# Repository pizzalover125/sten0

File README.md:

# sten0

sten0 is a minimalist stenography keyboard. it was meant to defeat the industry standard Uni v4 which is overpriced and unsymmetrical. it uses a 2-layer PCB and KMK firmware that converts to stenography with the industry-standard Plover firmware. 

### what is steno?
traditional stenography keyboards are keyboards used by transcribers in a courtroom to type extremely fast. hobbyists and now companies have created their own versions of steno keyboards. one can easily get 200 wpm using steno, demonstrated in the video here: https://www.youtube.com/watch?v=l8SWkR5y774. 

steno works by pressing multiple keys at once to create "chords" which create words. each key is associated with a specific sound. for example, to write "cat" press "K A T" all at once.

the company, stenokeyboards.com, is the leader of the steno industry with products that are pretty cool, but extremely expensive. worst of all, they are closed source. i wanted to make something better for cheaper.

### PCB + Schematic
I used KiCad 10.0 for the PCB design. The silkscreen art was created using https://www.fontspace.com/ and inputted to KiCad using the built-in Image Convertor tool.

### CAD
I used Onshape for the entire CAD. It features a front plate and a back plate. It is only 255.4 mm wide at its widest point, making it printable on a standard Bambu Lab A1 or any Bambu Lab 3d printer. Can be viewed here! https://cad.onshape.com/documents/f60da929d98268854f5791b9/w/b980d7f138533dbdb870e5ad/e/3b5277e683bbd7090a7e44ca?renderMode=0&uiState=6a166c62bcc75bd5e84998b5

### Firmware
The keyboard uses KMK. There is a standard keyboard matrix that links to standard QWERTY layout which will be converted to Steno layout with Plover firmware.

### Layout
This is the layout for both QWERTY and STENO. The blank keys are macro keys, meaning they can be mapped to anything!

### BOM
A detailed Bill of Materials can be found at https://docs.google.com/spreadsheets/d/1TjUF5DwXCz-duM485mYQtrJNJa8_saizqugbLS9kPO8/edit?gid=0#gid=0!

### Credits
Big thanks to Hack Club for funding the project + providing a LOT of help!

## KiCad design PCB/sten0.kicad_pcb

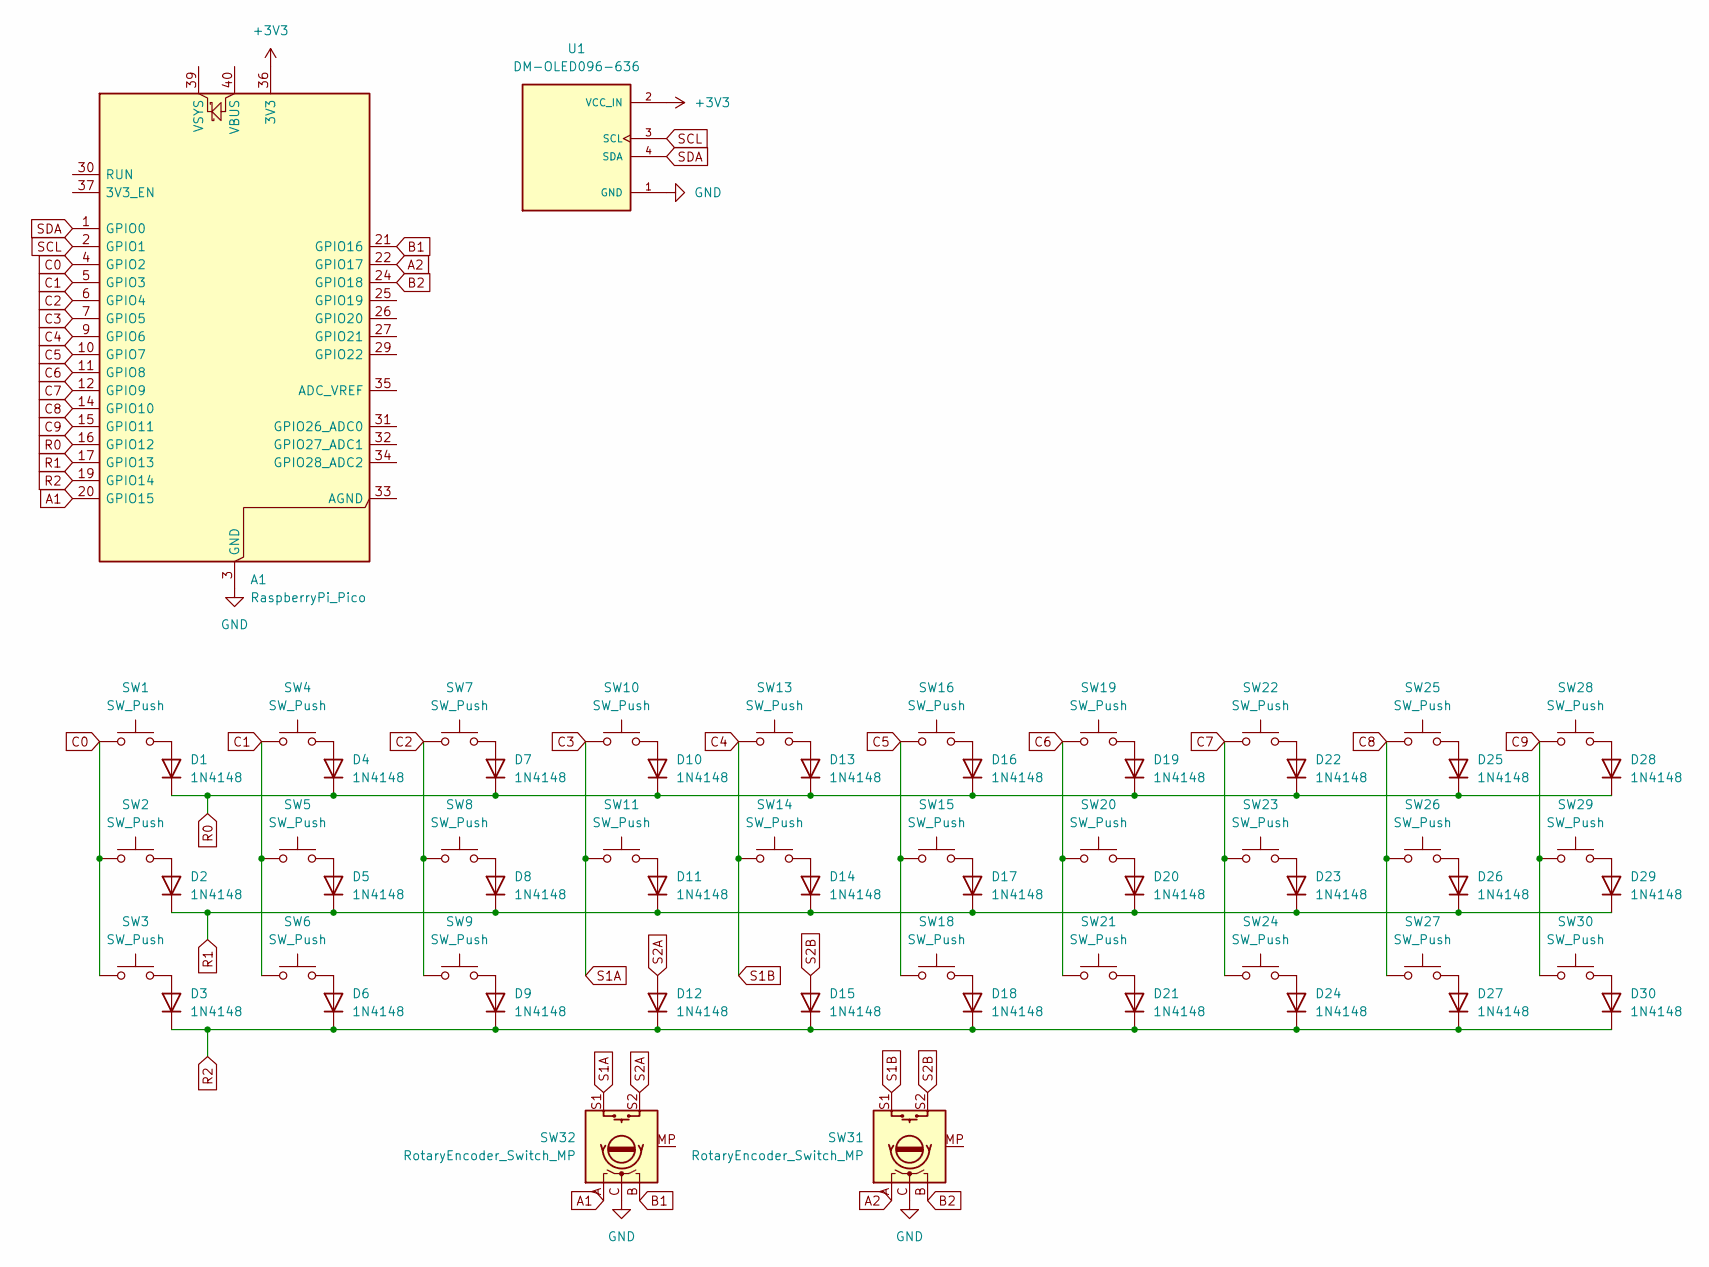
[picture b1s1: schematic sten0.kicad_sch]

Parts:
A1: RaspberryPi_Pico; RaspberryPi_Pico_Common_Unspecified
D1, D2, D3, D4, D5, D6, D7, D8, D9, D10, D11, D12, D13, D14, D15, D16, D17, D18, D19, D20, D21, D22, D23, D24, D25, D26, D27, D28, D29, D30: 1N4148; D_DO-35_SOD27_P7.62mm_Horizontal
SW1, SW2, SW3, SW4, SW5, SW6, SW7, SW8, SW9, SW10, SW11, SW13, SW14, SW15, SW16, SW18, SW19, SW20, SW21, SW22, SW23, SW24, SW25, SW26, SW27, SW28, SW29, SW30: SW_Push; SW_Cherry_MX_1.00u_PCB
SW31, SW32: RotaryEncoder_Switch_MP; RotaryEncoder_Alps_EC11E-Switch_Vertical_H20mm
U1: DM-OLED096-636; MODULE_DM-OLED096-636; PARTREV 2018-09-10

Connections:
+3V3: A1.36 (3V3), U1.2 (VCC_IN)
A1: A1.20 (GPIO15), SW32.A
A2: A1.22 (GPIO17), SW31.A
B1: A1.21 (GPIO16), SW32.B
B2: A1.24 (GPIO18), SW31.B
C0: A1.4 (GPIO2), SW1.1, SW2.1, SW3.1
C1: A1.5 (GPIO3), SW4.1, SW5.1, SW6.1
C2: A1.6 (GPIO4), SW7.1, SW8.1, SW9.1
C3: A1.7 (GPIO5), SW10.1, SW11.1, SW32.S1
C4: A1.9 (GPIO6), SW13.1, SW14.1, SW31.S1
C5: A1.10 (GPIO7), SW15.1, SW16.1, SW18.1
C6: A1.11 (GPIO8), SW19.1, SW20.1, SW21.1
C7: A1.12 (GPIO9), SW22.1, SW23.1, SW24.1
C8: A1.14 (GPIO10), SW25.1, SW26.1, SW27.1
C9: A1.15 (GPIO11), SW28.1, SW29.1, SW30.1
GND: A1.3 (GND), A1.8 (GND), A1.13 (GND), A1.18 (GND), A1.23 (GND), A1.28 (GND), A1.38 (GND), SW31.C, SW32.C, U1.1 (GND)
unnamed: D1.2 (A), SW1.2
unnamed: D2.2 (A), SW2.2
unnamed: D3.2 (A), SW3.2
unnamed: D4.2 (A), SW4.2
unnamed: D5.2 (A), SW5.2
unnamed: D6.2 (A), SW6.2
unnamed: D7.2 (A), SW7.2
unnamed: D8.2 (A), SW8.2
unnamed: D9.2 (A), SW9.2
unnamed: D10.2 (A), SW10.2
unnamed: D11.2 (A), SW11.2
unnamed: D13.2 (A), SW13.2
unnamed: D14.2 (A), SW14.2
unnamed: D16.2 (A), SW16.2
unnamed: D17.2 (A), SW15.2
unnamed: D18.2 (A), SW18.2
unnamed: D19.2 (A), SW19.2
unnamed: D20.2 (A), SW20.2
unnamed: D21.2 (A), SW21.2
unnamed: D22.2 (A), SW22.2
unnamed: D23.2 (A), SW23.2
unnamed: D24.2 (A), SW24.2
unnamed: D25.2 (A), SW25.2
unnamed: D26.2 (A), SW26.2
unnamed: D27.2 (A), SW27.2
unnamed: D28.2 (A), SW28.2
unnamed: D29.2 (A), SW29.2
unnamed: D30.2 (A), SW30.2
R0: A1.16 (GPIO12), D1.1 (K), D4.1 (K), D7.1 (K), D10.1 (K), D13.1 (K), D16.1 (K), D19.1 (K), D22.1 (K), D25.1 (K), D28.1 (K)
R1: A1.17 (GPIO13), D2.1 (K), D5.1 (K), D8.1 (K), D11.1 (K), D14.1 (K), D17.1 (K), D20.1 (K), D23.1 (K), D26.1 (K), D29.1 (K)
R2: A1.19 (GPIO14), D3.1 (K), D6.1 (K), D9.1 (K), D12.1 (K), D15.1 (K), D18.1 (K), D21.1 (K), D24.1 (K), D27.1 (K), D30.1 (K)
S2A: D12.2 (A), SW32.S2
S2B: D15.2 (A), SW31.S2
SCL: A1.2 (GPIO1), U1.3 (SCL)
SDA: A1.1 (GPIO0), U1.4 (SDA)

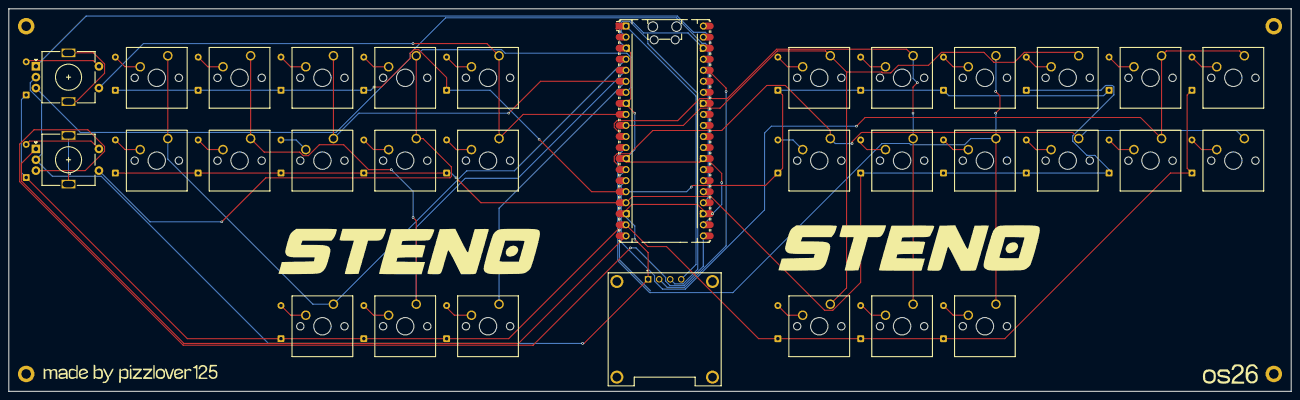
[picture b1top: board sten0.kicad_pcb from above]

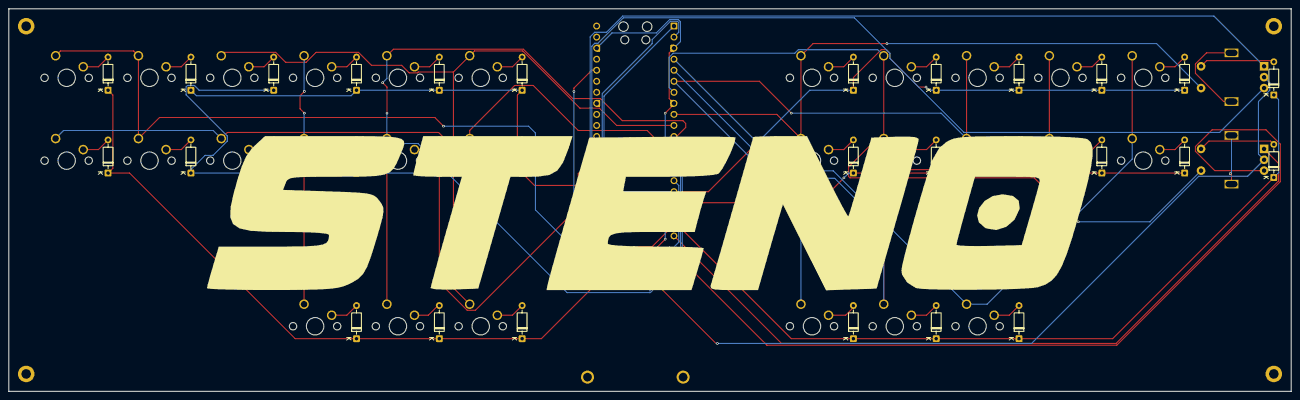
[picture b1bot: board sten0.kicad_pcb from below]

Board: 2 copper layers, 295.0 x 88.0 mm, 62 parts (30 on the bottom side), 51 nets.

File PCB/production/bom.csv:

Designator,Footprint,Quantity,Value,LCSC Part #
A1,RaspberryPi_Pico_Common_Unspecified,1,RaspberryPi_Pico,
"D1, D10, D11, D12, D13, D14, D15, D16, D17, D18, D19, D2, D20, D21, D22, D23, D24, D25, D26, D27, D28, D29, D3, D30, D4, D5, D6, D7, D8, D9",D_DO-35_SOD27_P7.62mm_Horizontal,30,1N4148,
"SW1, SW10, SW11, SW13, SW14, SW15, SW16, SW18, SW19, SW2, SW20, SW21, SW22, SW23, SW24, SW25, SW26, SW27, SW28, SW29, SW3, SW30, SW4, SW5, SW6, SW7, SW8, SW9",SW_Cherry_MX_1.00u_PCB,28,SW_Push,
"SW31, SW32",RotaryEncoder_Alps_EC11E-Switch_Vertical_H20mm,2,RotaryEncoder_Switch_MP,
U1,MODULE_DM-OLED096-636,1,DM-OLED096-636,

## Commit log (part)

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2026-05-13 Add description for sten0 steno board
    Added a brief description of the sten0 steno board.
2026-05-13 Update JOURNAL.md with project notes and plans
    Documented project progress and decisions regarding design, parts sourcing, and firmware.
2026-05-13 fixed formatting in journal
2026-05-13 Format journal entries with headings
    Updated date formatting and added headings for entries.
2026-05-14 added proper image
2026-05-14 fixed formatting
2026-05-15 Redesign Steno keyboard layout and complete PCB
    Redesigned the layout and completed schematic and PCB for the Steno keyboard. Added 3D models and routed the design.
2026-05-15 Update JOURNAL.md with firmware development notes
    Documented progress on firmware development, including keymap design and adjustments.
2026-05-15 Initialize firmware for keyboard with encoders and display
2026-05-15 Add initial firmware.py file
2026-05-15 Initialize keyboard with matrix and encoder setup
2026-05-15 Document progress on PCB design and challenges
    Added notes about mounting holes and PCB design progress, including software considerations and internet issues.
2026-05-17 Update journal with KiCad rendering progress
    Documented progress on KiCad rendering and design updates, including issues faced and solutions implemented.
2026-05-17 Update journal entry date from 5/17 to 5/16
2026-05-17 Update JOURNAL.md with keyboard design notes
    Added additional notes and images related to keyboard design and BOM adjustments.
2026-05-17 Update JOURNAL.md with polishing details and time
    Updated time spent on polishing and BOM from 60 to 140 minutes. Added details about PCB routing changes and 3D modeling of key and keycap.
2026-05-17 added evrything
2026-05-17 added images
    Added images and additional details about PCB, CAD, and firmware.
2026-05-17 Add explanation of steno keyboards and project motivation
    Added a section explaining traditional stenography keyboards and the motivation behind creating a budget-friendly steno board.
2026-05-17 Fix README title for clarity
2026-05-17 Update JOURNAL.md with new entry
    Added journal entry about steno keyboard idea and plan.
2026-05-18 Adjust time entries in JOURNAL.md
    Updated time spent on tasks and corrected entry duration.
2026-05-18 updated image
2026-05-23 added stuff
2026-05-23 finished v2!
